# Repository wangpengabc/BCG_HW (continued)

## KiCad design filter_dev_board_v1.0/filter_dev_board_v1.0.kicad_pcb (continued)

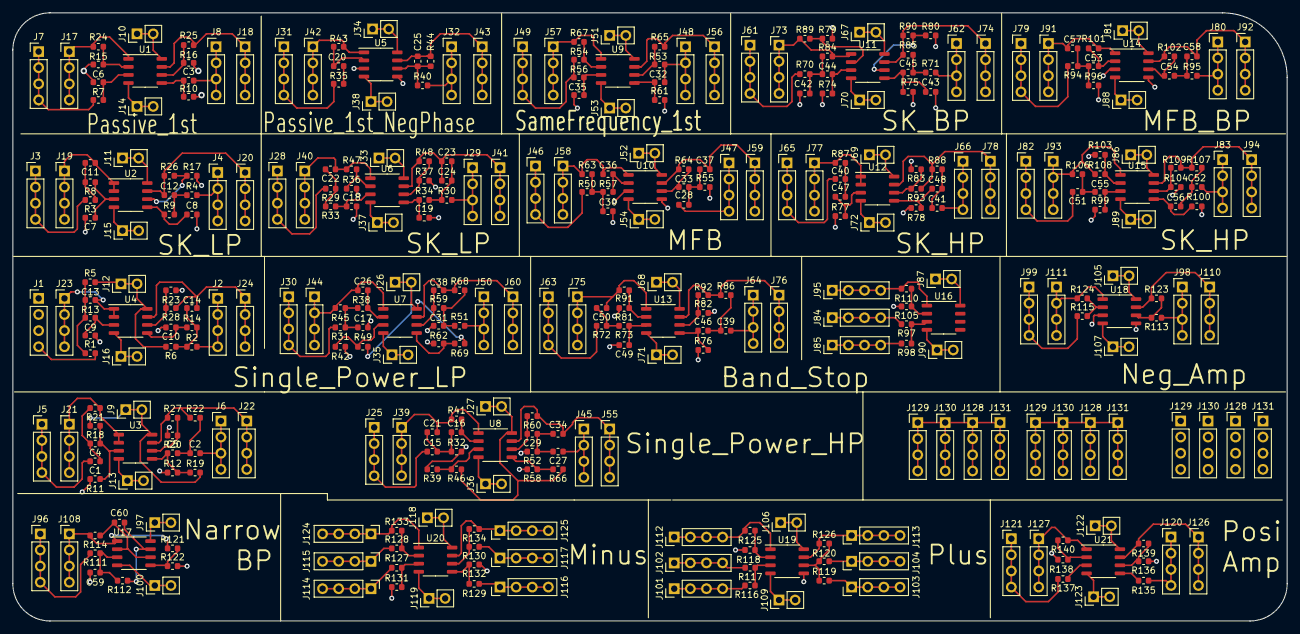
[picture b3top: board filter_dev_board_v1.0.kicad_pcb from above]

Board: 2 copper layers, 200.7 x 95.8 mm, 360 parts (0 on the bottom side), 222 nets.

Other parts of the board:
J128#2, J128#3, J129#2, J129#3, J130#2, J130#3, J131#2, J131#3: Conn_01x04; PinHeader_1x04_P2.54mm_Vertical

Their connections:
GND: J128#3.1, J128#3.2, J128#3.3, J128#3.4, J129#3.1, J129#3.2, J129#3.3, J129#3.4, J130#3.1, J130#3.2, J130#3.3, J130#3.4, J131#3.1, J131#3.2, J131#3.3, J131#3.4; also elsewhere on the board

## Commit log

2020-11-19 add BCG_piezoV1.0
2020-11-19 add filter
2020-11-24 add c8t6_mini
2020-11-24 refresh BCGPiezo_v1.0
2020-11-24 add new BCG_Piezo_V1.0
2020-11-25 Update README.md
    test git
2020-11-25 local test
